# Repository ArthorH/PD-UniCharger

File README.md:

# Universal Type C charger for every battery type !

## Key technologies:
 &nbsp;&nbsp;&nbsp;&nbsp; &nbsp;&nbsp;&nbsp;&nbsp;
---
# Features
- CC CV regulation
- Multiple settings
- USB C power delivery 20v
- Reverse polarity battery protection
---
# BLOCK DIAGRAM

# How it works:
## IP2721
IP2721 negotiates voltage set by J2 (short 20v open 15v) and outputs it to VBUS_PD

## CC CV Stepdown
Typycal LM358 based CC CV regulation circuit

### CC CV in operation
CC            |  CV
:-------------------------:|:-------------------------:
  |   

## Battery reverse polarity protection 
Battery protection circuit works as SR latch with one of latching elements being P-MOS that outputs voltage to battery.
One downside to using this schematic is that charger needs to be powered down in order to "delatch" protection circuit, otherwise it may not work if battery had been disconected and reconnected again. This issue will be fixed in upcomming REV-B. 

### How it works
#### Phase 1
Power on state. Circuit is delatched. 

#### Phase 2
Connected battery starts to turn on transistor that turns on photocoupler. Circuit latches and starts charging battery, given it can provide 20ma of current and it sits above 1.5v.

## Usage
Intended use is keychain charger to charge for example car battery form powerbank that is capable of PD output.

It is advantageous to carry a portable charging board in a vehicle or backpack as a contingency, even though its charging efficiency may not be optimal.

# License 
CERN-OHL-P
(CERN Open Hardware Licence Version 2 - Permissive)

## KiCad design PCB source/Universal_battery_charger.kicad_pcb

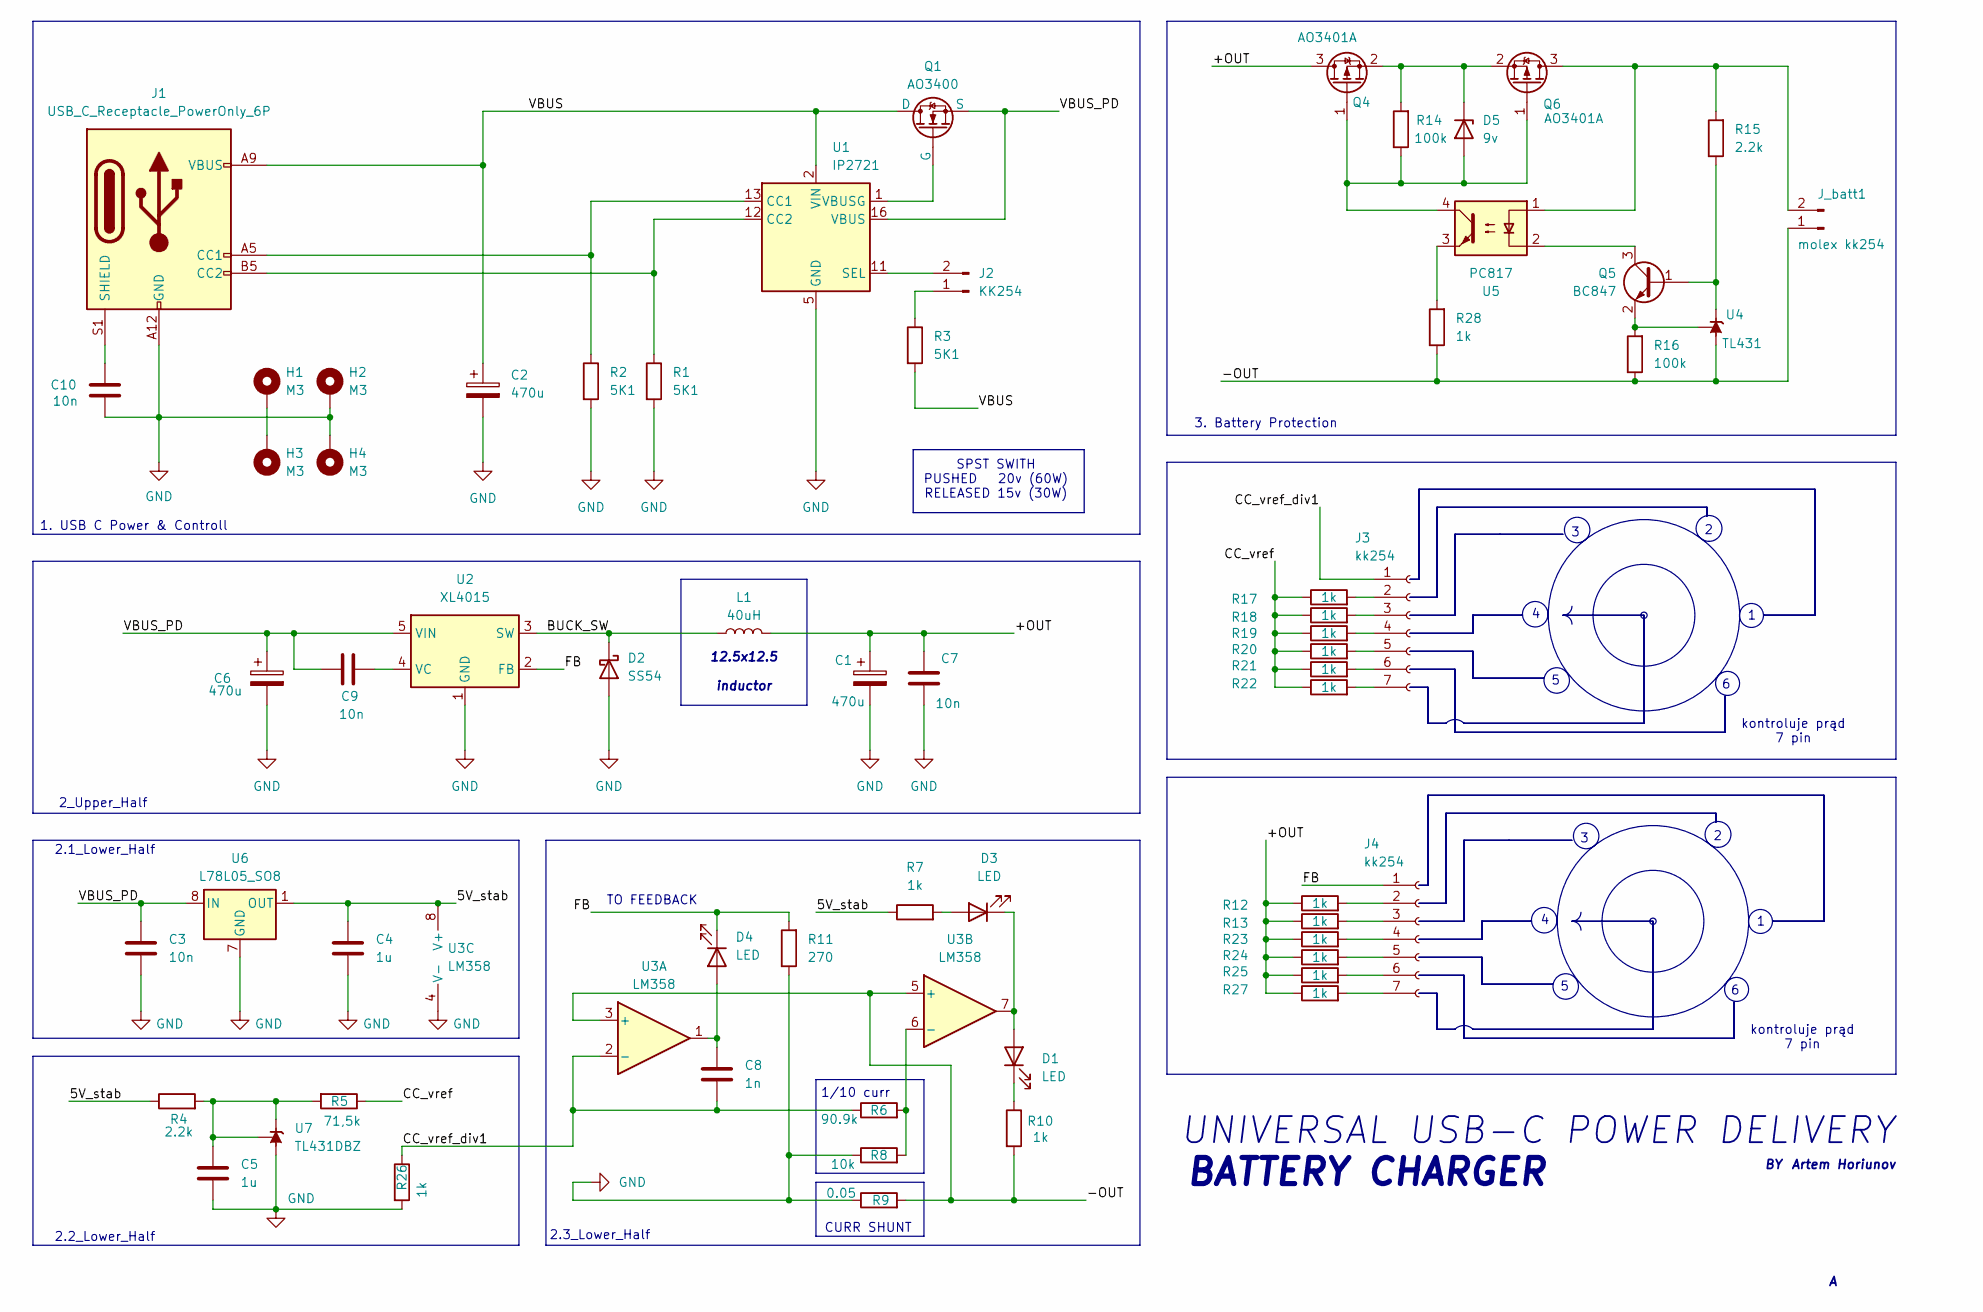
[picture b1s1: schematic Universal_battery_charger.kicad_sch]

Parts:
C1, C2, C6: 470u; CP_Elec_10x10
C3, C7, C9, C10: 10n; C_0603_1608Metric_Pad1.08x0.95mm_HandSolder
C4, C5: 1u; C_0805_2012Metric_Pad1.18x1.45mm_HandSolder
C8: 1n; C_0603_1608Metric_Pad1.08x0.95mm_HandSolder
D1, D3, D4: LED; LED_0603_1608Metric
D2: SS54; D_SMA
D5: 9v; D_SOD-123F
H1, H2, H3, H4: M3; MountingHole_3.2mm_M3_Pad_Via
J1: USB_C_Receptacle_PowerOnly_6P; USB_C_Receptacle_GCT_USB4135-GF-A_6P_TopMnt_Horizontal
J2: KK254; PinHeader_1x02_P2.54mm_Vertical
J3, J4: kk254; Molex_KK-254_AE-6410-07A_1x07_P2.54mm_Vertical
J_batt1: molex kk254; PinHeader_1x02_P2.54mm_Vertical
L1: 40uH; L_Bourns_SRR1260
Q1: AO3400; SOT-23
Q4, Q6: AO3401A; SOT-23
Q5: BC847; SOT-23
R1, R2, R3: 5K1; R_0603_1608Metric_Pad0.98x0.95mm_HandSolder
R4, R15: 2.2k; R_0603_1608Metric_Pad0.98x0.95mm_HandSolder
R5: 71,5k; R_0603_1608Metric_Pad0.98x0.95mm_HandSolder
R6: 90.9k; R_0603_1608Metric_Pad0.98x0.95mm_HandSolder
R7, R10, R12, R13, R17, R18, R19, R20, R21, R22, R23, R24, R25, R26, R27, R28: 1k; R_0603_1608Metric_Pad0.98x0.95mm_HandSolder
R8: 10k; R_0603_1608Metric_Pad0.98x0.95mm_HandSolder
R9: 0.05; R_2512_6332Metric_Pad1.40x3.35mm_HandSolder
R11: 270; R_0603_1608Metric_Pad0.98x0.95mm_HandSolder
R14, R16: 100k; R_0603_1608Metric_Pad0.98x0.95mm_HandSolder
U1: IP2721; TSSOP-16_4.4x5mm_P0.65mm
U2: XL4015; TO-263-5_TabPin3
U3: LM358; SO-8_3.9x4.9mm_P1.27mm
U4: TL431; SOT-23
U5: PC817; DIP-4_W7.62mm
U6: L78L05_SO8; SOIC-8_3.9x4.9mm_P1.27mm
U7: TL431DBZ; SOT-23

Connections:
/5V_stab: C4.1, R4.1, R7.1, U3.8 (V+), U6.1 (OUT)
/+OUT: C1.1, C7.1, L1.2, Q4.3 (D), R12.1, R13.1, R23.1, R24.1, R25.1, R27.1
/-OUT: J_batt1.1, R9.2, R10.2, R16.1, R28.1, U3.3 (+), U3.5 (+), U4.3 (A)
/BUCK_SW: D2.1 (K), L1.1, U2.3 (SW)
/CC_vref: R5.1, R17.1, R18.1, R19.1, R20.1, R21.1, R22.1
/CC_vref_div1: C8.2, J3.1, R6.1, R26.1, U3.2 (-)
/FB: D4.1 (K), J4.1, R11.2, U2.2 (FB)
/VBUS: C2.1, J1.A9 (VBUS), J1.B9 (VBUS), Q1.2 (D), R3.2, U1.2 (VIN)
/VBUS_PD: C3.1, C6.1, C9.1, Q1.3 (S), U1.16 (VBUS), U2.5 (VIN), U6.8 (IN)
unnamed: D1.2 (A), D3.1 (K), U3.7
unnamed: D1.1 (K), R10.1
unnamed: D3.2 (A), R7.2
unnamed: C8.1, D4.2 (A), U3.1
unnamed: D5.2 (A), Q4.1 (G), Q6.1 (G), R14.1, U5.4
unnamed: D5.1 (K), Q4.2 (S), Q6.2 (S), R14.2
unnamed: J1.A5 (CC1), R2.1, U1.13 (CC1)
unnamed: J1.B5 (CC2), R1.1, U1.12 (CC2)
unnamed: C10.2, J1.S1 (SHIELD)
unnamed: J2.1, R3.1
unnamed: J2.2, U1.11 (SEL)
unnamed: J3.2, R17.2
unnamed: J3.3, R18.2
unnamed: J3.4, R19.2
unnamed: J3.5, R20.2
unnamed: J3.6, R21.2
unnamed: J3.7, R22.2
unnamed: J4.2, R12.2
unnamed: J4.3, R13.2
unnamed: J4.4, R23.2
unnamed: J4.5, R24.2
unnamed: J4.6, R25.2
unnamed: J4.7, R27.2
unnamed: J_batt1.2, Q6.3 (D), R15.2, U5.1
unnamed: Q1.1 (G), U1.1 (VBUSG)
unnamed: Q5.1 (B), R15.1, U4.2 (K)
unnamed: Q5.3 (C), U5.2
unnamed: Q5.2 (E), R16.2, U4.1 (REF)
unnamed: R28.2, U5.3
unnamed: C9.2, U2.4 (VC)
unnamed: R6.2, R8.2, U3.6 (-)
unnamed: C5.1, R4.2, R5.2, U7.1 (REF), U7.2 (K)

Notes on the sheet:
BATTERY CHARGER
1/10 curr
2.2_Lower_Half
TO FEEDBACK
kontroluje prąd 7 pin
2.1_Lower_Half
SPST SWITH PUSHED 20v (60W) RELEASED 15v (30W)
UNIVERSAL USB-C POWER DELIVERY
3. Battery Protection
2.3_Lower_Half
CURR SHUNT
12.5x12.5 inductor
1. USB C Power & Controll
2_Upper_Half
Artem Horiunov

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
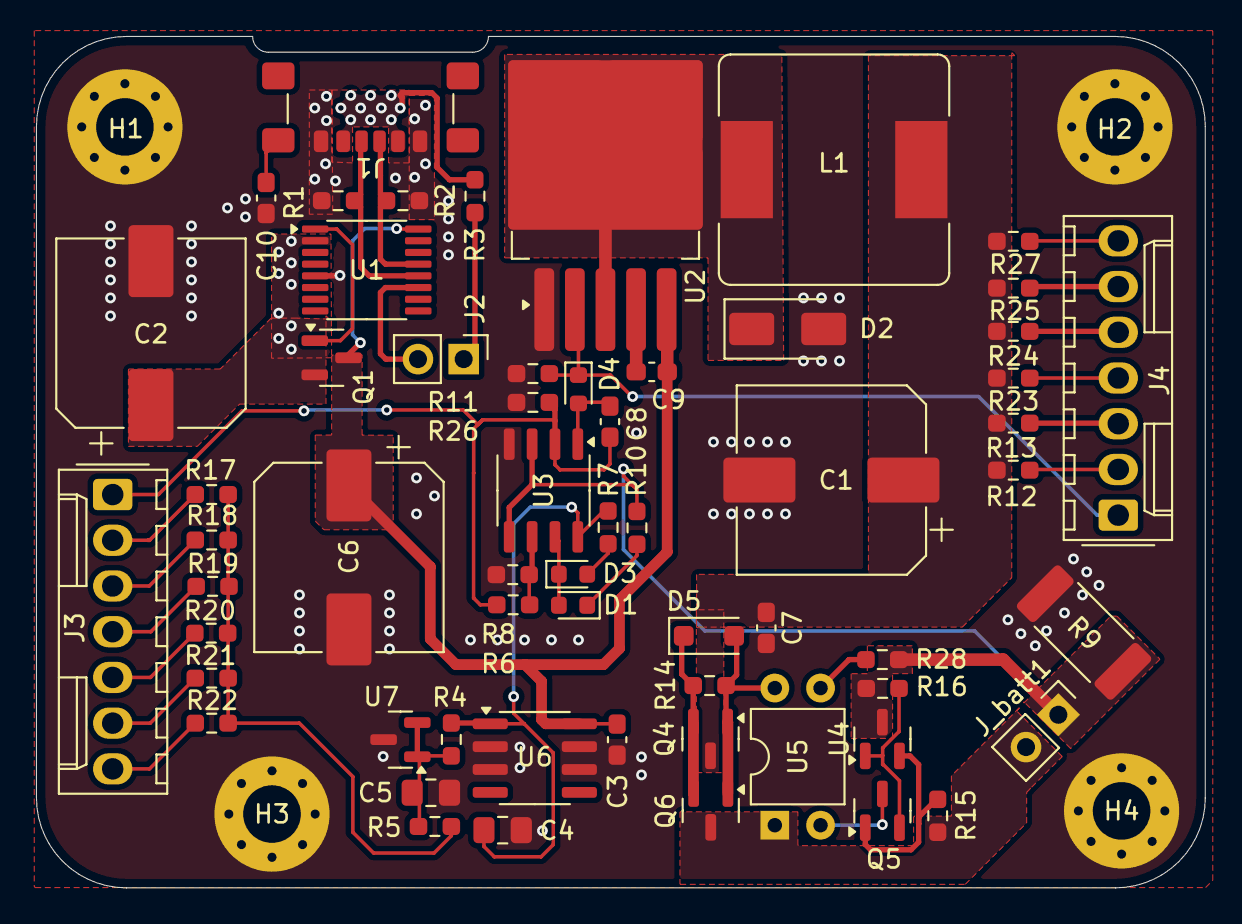
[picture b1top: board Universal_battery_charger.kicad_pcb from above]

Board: 2 copper layers, 64.9 x 47.3 mm, 64 parts (0 on the bottom side), 42 nets.

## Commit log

2024-08-13 REV A
2024-08-13 Github preview bug.md
2024-12-28 Add render to MD
2025-02-14 Do Cleanup
2025-02-14 Fix readme
